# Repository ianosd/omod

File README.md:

# omod - Open Source Motor Driver
A motor driver used to command two motors. It avoids the complications of an H-bridge
by using a relay to switch the command direction (at the cost of making switching slower).
Checkout [the schematic pdf](schematic.pdf) for a quick impression.
You need KiCad to open the project files.

Here is a picture of the PCB layout:

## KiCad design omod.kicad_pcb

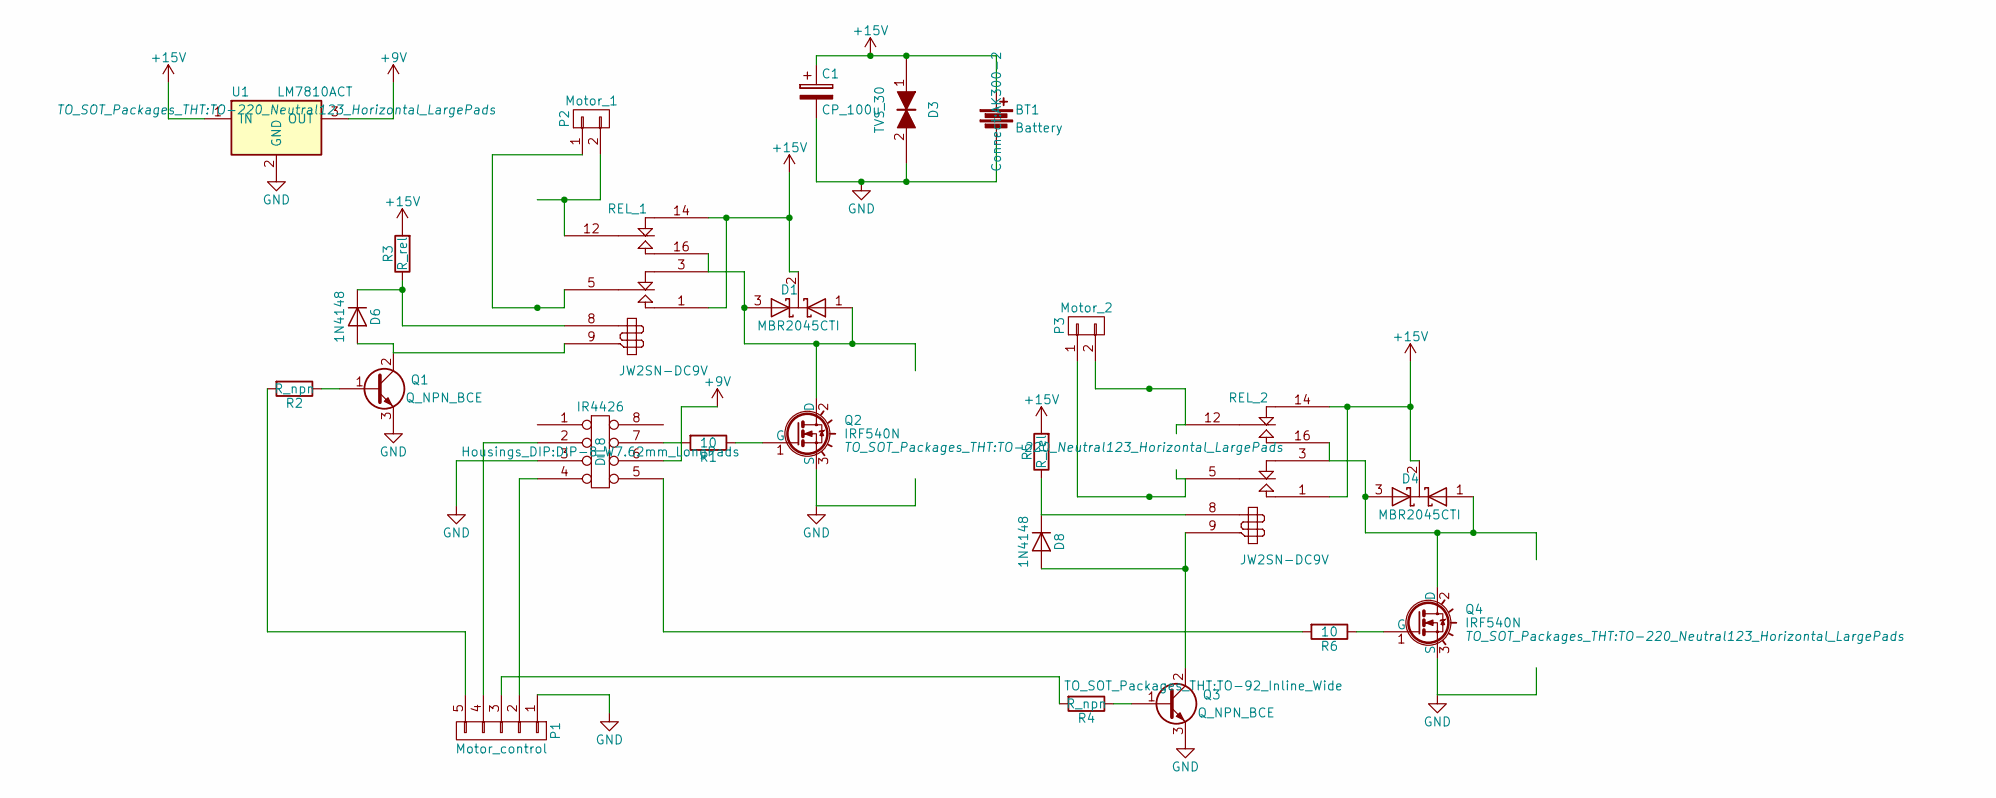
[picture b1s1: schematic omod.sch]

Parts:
BT1: Battery; AK300-2
C1: CP_100u; C_Radial_D8_L11.5_P3.5
D1, D4: MBR2045CTI; TO-220_Neutral123_Horizontal_LargePads
D3: TVS_30; Diode_DO-35_SOD27_Horizontal_RM10
D6, D8: 1N4148; Diode_DO-35_SOD27_Horizontal_RM10
IR4426: DIL8; DIP-8_W7.62mm_LongPads
P1: Motor_control; Pin_Header_Angled_1x05
P2: Motor_1; AK300-2
P3: Motor_2; AK300-2
Q1, Q3: Q_NPN_BCE; TO-92_Inline_Wide
Q2, Q4: IRF540N; TO-220_Neutral123_Horizontal_LargePads
R1: 10; Resistor_Horizontal_RM15mm
R2: R_npn; Resistor_Horizontal_RM10mm
R3, R5: R_rel; Resistor_Horizontal_RM10mm
R4: R_npn; Resistor_Horizontal_RM20mm
R6: 10; Resistor_Horizontal_RM10mm
REL_1, REL_2: JW2SN-DC9V; Relay_DPDT_Schrack-RT2_RM5mm_mine
U1: LM7810ACT; TO-220_Neutral123_Horizontal_LargePads

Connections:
+9V: IR4426.6 (Vs), U1.3 (OUT)
+15V: BT1.1, C1.1, D1.2 (K), D3.1, D4.2 (K), R3.2, R5.2, REL_1.1 (T1), REL_1.14 (R2), REL_2.1 (T1), REL_2.14 (R2), U1.1 (IN)
GND: BT1.2, C1.2, D3.2, IR4426.3 (GND), P1.1, Q1.3 (E), Q2.3 (S), Q3.3 (E), Q4.3 (S), U1.2 (GND)
unnamed: D1.1 (A), D1.3 (A), Q2.2 (D), REL_1.3 (R1), REL_1.16 (T2)
unnamed: D4.1 (A), D4.3 (A), Q4.2 (D), REL_2.3 (R1), REL_2.16 (T2)
unnamed: D6.1 (K), R3.1, REL_1.8
unnamed: D6.2 (A), Q1.2 (C), REL_1.9
unnamed: P2.2, REL_1.12 (C2)
unnamed: P2.1, REL_1.5 (C1)
unnamed: D8.1 (K), R5.1, REL_2.8
unnamed: D8.2 (A), Q3.2 (C), REL_2.9
unnamed: P3.2, REL_2.12 (C2)
unnamed: P3.1, REL_2.5 (C1)
unnamed: IR4426.2 (INA), P1.4
unnamed: IR4426.4 (INB), P1.2
unnamed: IR4426.5 (OUTB), R6.2
unnamed: IR4426.7 (OUTA), R1.2
unnamed: P1.3, R4.2
unnamed: P1.5, R2.2
unnamed: Q1.1 (B), R2.1
unnamed: Q2.1 (G), R1.1
unnamed: Q3.1 (B), R4.1
unnamed: Q4.1 (G), R6.1

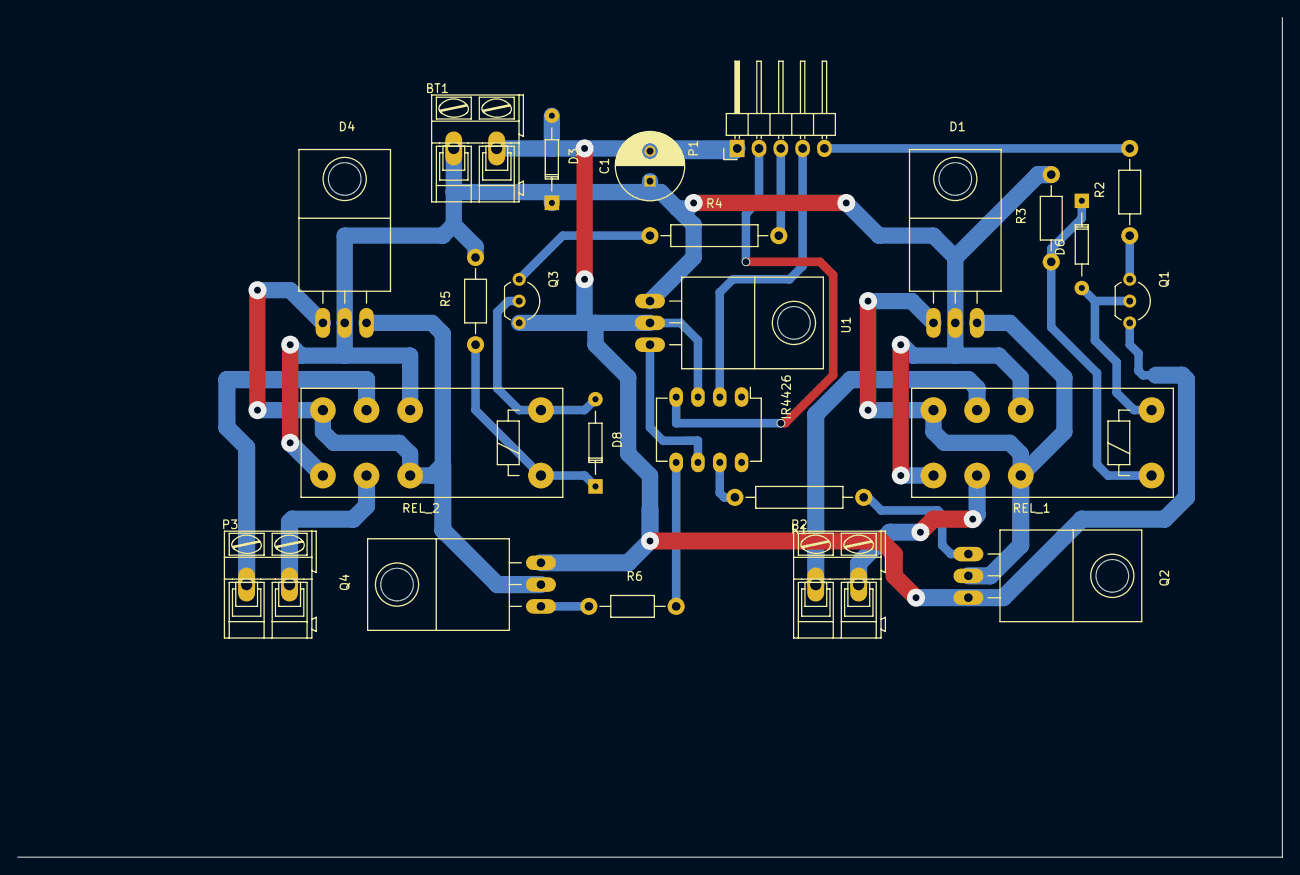
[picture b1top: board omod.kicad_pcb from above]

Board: 2 copper layers, 147.3 x 97.8 mm, 24 parts (0 on the bottom side), 23 nets.

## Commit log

2017-07-24 old files added
2017-07-25 simulation init
2017-08-07 ok simulation and removed TVS
2017-08-07 before new pcb
2024-12-30 Improve README
